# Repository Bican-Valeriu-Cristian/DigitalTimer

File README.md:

# Digital Timer

The project involves a digital timer that counts up to one minute. Each counter's 4-bit output is fed into a binary-to-7-segment decoder, enabling number display on 7-segment displays. 
The circuit includes switches for starting/stopping the timer and resetting the count.

## Description

This circuit diagram represents a digital timer capable of counting seconds up to one minute. The circuit operates by generating a clock signal with a precise frequency of 1 Hz (once per second) using an oscillator based on the NE555 timer. This signal is connected to the count-up input of an integrated circuit counter. Since the counter dedicated to seconds has a 4-bit output, it can count up to 15. Therefore, it requires conditioning with logic circuits to prevent it from exceeding the value of 10. Each time this number is reached, a count-up signal is also sent to a second counter dedicated to tens of seconds. This counter also requires logic conditioning, but this time up to the value of 6.

The 4 bits produced by each counter are then fed into a binary-to-7-segment decoder, which finally allows the numbers to be displayed on 7-segment displays. Additionally, the circuit includes two switches, one for starting and stopping the timer and another for resetting the count.

## Contents

| File/folder | Description |
|-------------|-------------|
| `PCB.kicad_sch`       | Schematic |
| `PCB.kicad_pcb`       | PCB editor |
| `gerber`         | Altium Designer schematics, PCB layout, and supporting project files
| `README.md` | This README file. |
| `LICENSE`   | The license for the project. |

## Tools

First step:
The schematic for this project was created using KiCad software.

Next was drawing the layout:

  -The PCB is a 8 cm x 8 cm 2-layer board.

  -It has a GND copper plane on both layers.

  -All signal traces are 0.254 mm, while the 5V power trace is double the size, at 0.508 mm.

  -Proper names were added for the various components, along with description text and a nice drawing.

The final steps were to order the parts, the PCB, and assemble the board.

  -The various components were ordered from TME
  
  -The PCB was ordered from Jlcpcb

## Bill of materials

-2x 7-segment displays

-2x 10nF ceramic capacitors

-1x 1uF electrolytic capacitor

-2x push switches

-2x header pins

-2x 4-bit tri-state registers

-2x 4-bit BCD decoders

-2x 4-bit counters

-2x quad AND gate chips

-1x quad NOR gate chip

-1x dual JK flip-flop chip

-Various resistors

## Final statistics
  
Total hours of work:

  Designing schematic and testing: 3 hours
  
  Making layout: 3 hours
  
  Assembling PCB: 5 hours

## Extra photos

## License

For details on license, see LICENSE in this directory.

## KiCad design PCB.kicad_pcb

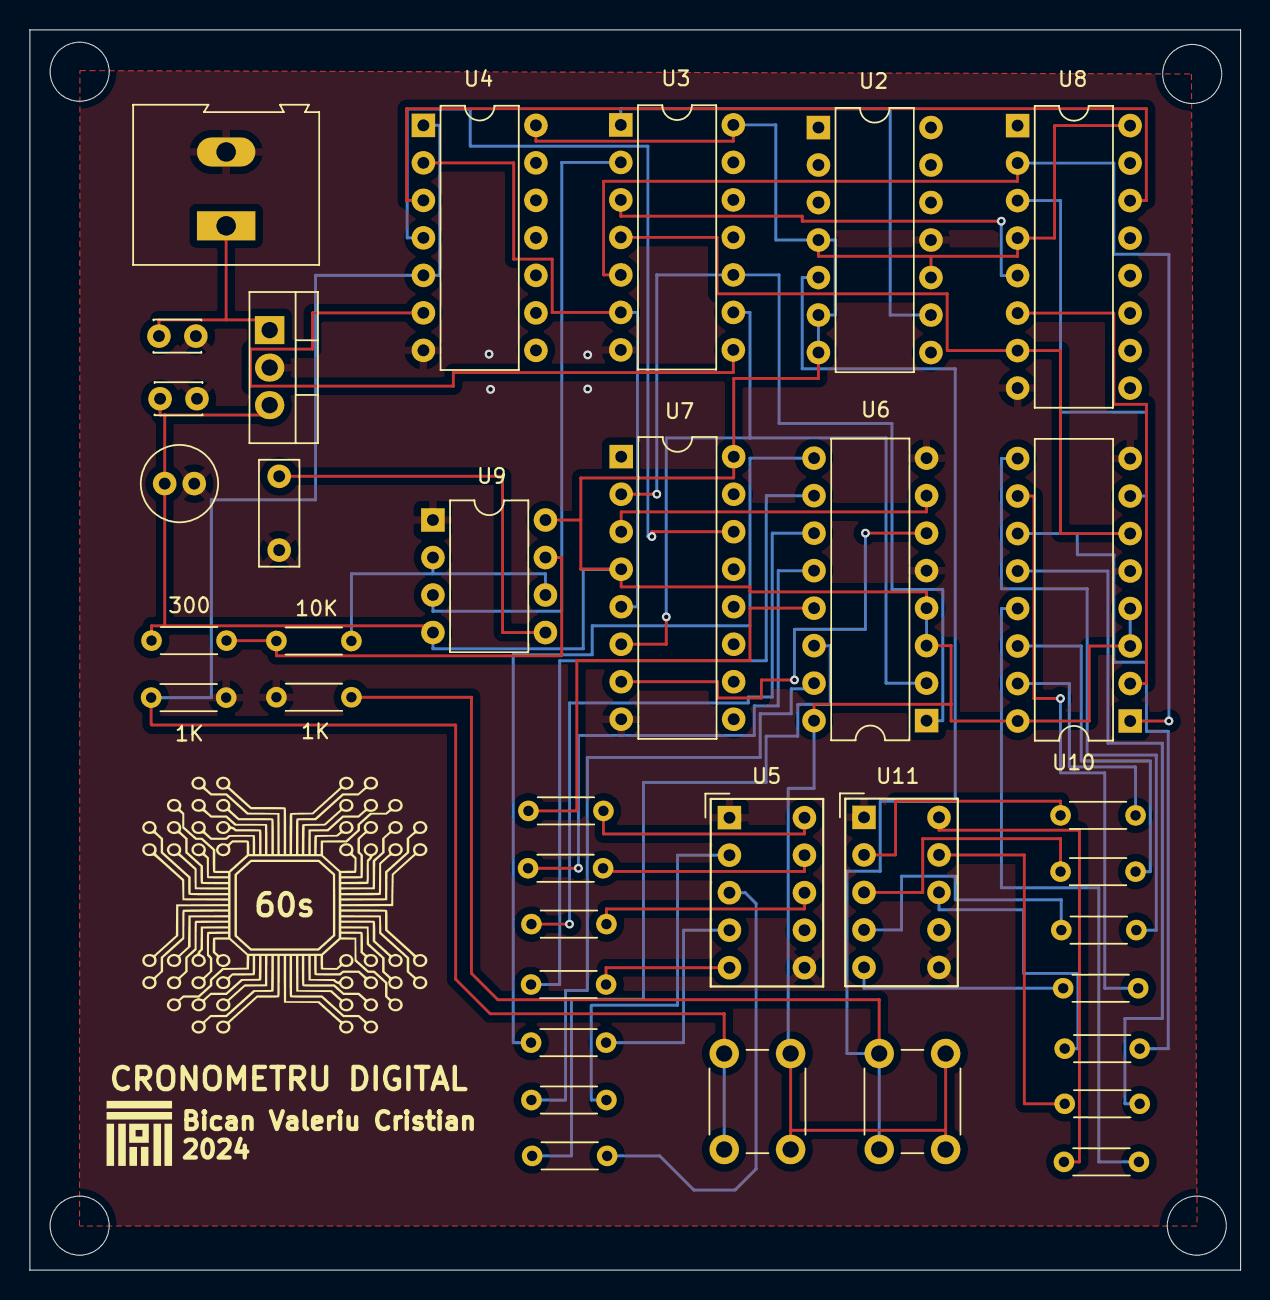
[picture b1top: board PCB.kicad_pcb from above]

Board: 2 copper layers, 82.0 x 84.0 mm, 37 parts (0 on the bottom side), 51 nets.

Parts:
1K, 1K#2: 1k; R_Axial_DIN0204_L3.6mm_D1.6mm_P5.08mm_Horizontal
10K: 10k; R_Axial_DIN0204_L3.6mm_D1.6mm_P5.08mm_Horizontal
60s: LOGO; 2
300: 300; R_Axial_DIN0204_L3.6mm_D1.6mm_P5.08mm_Horizontal
C1, C2: 100n; C_Disc_D3.0mm_W2.0mm_P2.50mm
C3: 10n; C_Rect_L7.0mm_W2.5mm_P5.00mm
C4: 47u; C_Radial_D5.0mm_H11.0mm_P2.00mm
J1: Screw_Terminal_01x02; TerminalBlock_Altech_AK300-2_P5.00mm
R1, R2, R3, R4, R5, R6, R7, R8, R9, R10, R11, R12, R13, R14: 300R; R_Axial_DIN0204_L3.6mm_D1.6mm_P5.08mm_Horizontal
SW1, SW2: SW_Push; SW_PUSH_6mm
U1: L7805; TO-220-3_Vertical
U2: 74LS73; DIP-14_W7.62mm
U3: 74LS08; DIP-14_W7.62mm
U4: 4071; DIP-14_W7.62mm
U5, U11: HDSP-7403; HDSP-7401
U6, U10: 4511; DIP-16_W7.62mm
U7, U8: 74LS193; DIP-16_W7.62mm
U9: NE555D; DIP-8_W7.62mm

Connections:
+5V: 300.2, C1.1, C4.2, SW1.1, SW2.1, U1.3 (OUT), U2.4 (VCC), U2.6 (~R), U2.7 (J), U2.10 (K), U3.14 (VCC), U4.14 (VDD), U6.3 (~LT), U6.4 (~BI), U6.16 (Vdd), U7.4 (DOWN), U7.16 (VCC), U8.4 (DOWN), U8.16 (VCC), U9.4 (R), U9.8 (VCC), U10.3 (~LT), U10.4 (~BI), U10.16 (Vdd)
GND: 1K.2, 1K#2.2, C1.2, C2.2, C3.1, C4.1, J1.2, U1.2 (GND), U2.11 (GND), U3.7 (GND), U4.7 (VSS), U5.1 (CC), U5.6 (CC), U6.5 (~EL), U6.8 (Vss), U7.8 (GND), U8.8 (GND), U9.1 (GND), U10.5 (~EL), U10.8 (Vss), U11.1 (CC), U11.6 (CC)
unnamed: C2.1, J1.1, U1.1 (IN)
unnamed: 1K.1, SW1.2, U4.1, U4.5
unnamed: 1K#2.1, SW2.2, U2.5 (C)
unnamed: U2.9 (Q), U3.1
unnamed: U3.8, U4.6
unnamed: R1.2, U5.10 (A)
unnamed: R2.2, U5.9 (B)
unnamed: R3.2, U5.8 (C)
unnamed: R4.2, U5.5 (D)
unnamed: R5.2, U5.4 (E)
unnamed: R6.2, U5.2 (F)
unnamed: R7.2, U5.3 (G)
unnamed: U6.7 (DA), U7.3 (QA)
unnamed: U3.10, U6.1 (DB), U7.2 (QB)
unnamed: U3.9, U6.2 (DC), U7.6 (QC)
unnamed: U6.6 (DD), U7.7 (QD)
unnamed: R1.1, U6.13 (Qa)
unnamed: R2.1, U6.12 (Qb)
unnamed: R3.1, U6.11 (Qc)
unnamed: R4.1, U6.10 (Qd)
unnamed: R5.1, U6.9 (Qe)
unnamed: R6.1, U6.15 (Qf)
unnamed: R7.1, U6.14 (Qg)
unnamed: U4.4, U7.14 (CLR)
unnamed: U3.6, U4.2, U7.5 (UP)
unnamed: U4.3, U8.14 (CLR)
unnamed: U3.3, U8.5 (UP)
unnamed: C3.2, U9.5 (CV)
unnamed: 10K.2, 300.1, U9.7 (DIS)
unnamed: U3.2, U9.3 (Q)
unnamed: 10K.1, U9.2 (TR), U9.6 (THR)
unnamed: U8.3 (QA), U10.7 (DA)
unnamed: U3.5, U8.2 (QB), U10.1 (DB)
unnamed: U8.6 (QC), U10.2 (DC)
unnamed: U3.4, U8.7 (QD), U10.6 (DD)
unnamed: R8.1, U10.13 (Qa)
unnamed: R9.1, U10.12 (Qb)
unnamed: R10.1, U10.11 (Qc)
unnamed: R11.1, U10.10 (Qd)
unnamed: R12.1, U10.9 (Qe)
unnamed: R13.1, U10.15 (Qf)
unnamed: R14.1, U10.14 (Qg)
unnamed: R8.2, U11.10 (A)
unnamed: R9.2, U11.9 (B)
unnamed: R10.2, U11.8 (C)
unnamed: R11.2, U11.5 (D)
unnamed: R12.2, U11.4 (E)
unnamed: R13.2, U11.2 (F)
unnamed: R14.2, U11.3 (G)

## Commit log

2024-07-14 Rename practica.kicad_prl to PCB.kicad_prl
2024-07-14 Rename practica.kicad_pro to PCB.kicad_pro
